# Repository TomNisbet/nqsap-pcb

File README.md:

# NQSAP-PCB

A multi-PCB version of the [NQSAP 8-bit computer](https://tomnisbet.github.io/nqsap/)

Visit the [NQSAP-PCB documentation pages](https://tomnisbet.github.io/nqsap-pcb/) for
detailed design notes and schematics.

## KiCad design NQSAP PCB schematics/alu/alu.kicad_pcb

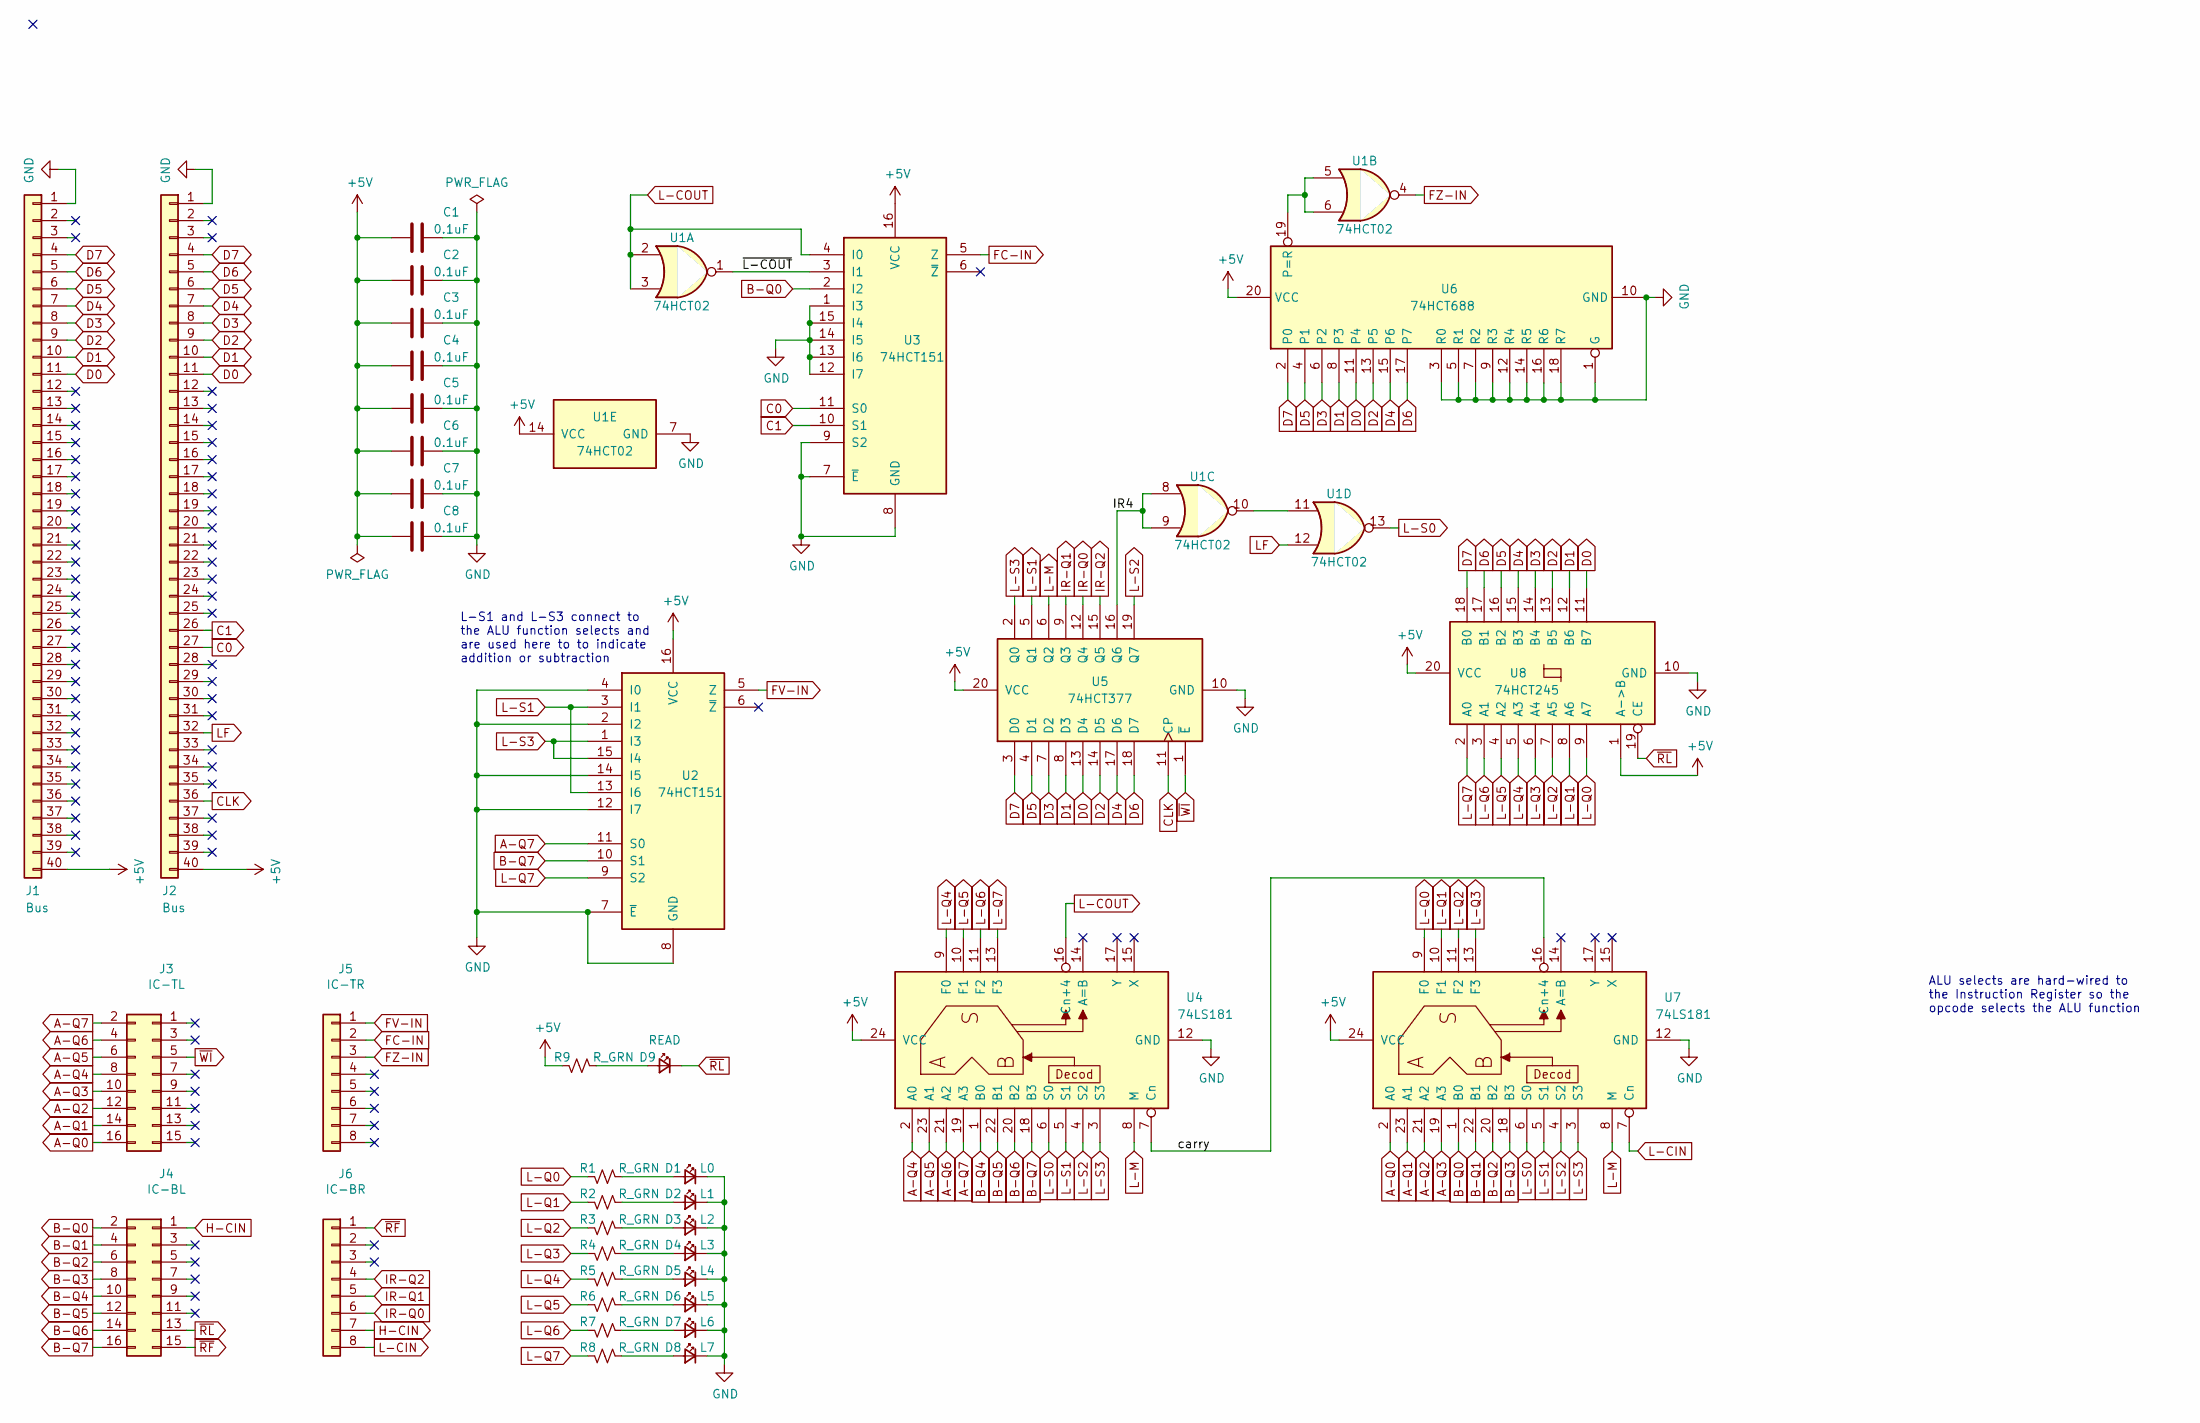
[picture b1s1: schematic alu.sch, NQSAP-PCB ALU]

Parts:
C1, C2, C3, C4, C5, C6, C7, C8: 0.1uF; C_0805_2012Metric_Pad1.18x1.45mm_HandSolder
D1: L0; LED_0805_2012Metric_Pad1.15x1.40mm_HandSolder
D2: L1; LED_0805_2012Metric_Pad1.15x1.40mm_HandSolder
D3: L2; LED_0805_2012Metric_Pad1.15x1.40mm_HandSolder
D4: L3; LED_0805_2012Metric_Pad1.15x1.40mm_HandSolder
D5: L4; LED_0805_2012Metric_Pad1.15x1.40mm_HandSolder
D6: L5; LED_0805_2012Metric_Pad1.15x1.40mm_HandSolder
D7: L6; LED_0805_2012Metric_Pad1.15x1.40mm_HandSolder
D8: L7; LED_0805_2012Metric_Pad1.15x1.40mm_HandSolder
D9: READ; LED_0805_2012Metric_Pad1.15x1.40mm_HandSolder
J1, J2: Bus; PinHeader_1x40_P2.54mm_Vertical
J3: IC-TL; PinHeader_2x08_P2.54mm_Vertical
J4: IC-BL; PinHeader_2x08_P2.54mm_Vertical
J5: IC-TR; PinHeader_1x08_P2.54mm_Vertical
J6: IC-BR; PinHeader_1x08_P2.54mm_Vertical
R1, R2, R3, R4, R5, R6, R7, R8, R9: R_GRN; R_0805_2012Metric_Pad1.20x1.40mm_HandSolder
U1: 74HCT02; DIP-14_W7.62mm
U2, U3: 74HCT151; DIP-16_W7.62mm
U4, U7: 74LS181; DIP-24_W15.24mm_Socket
U5: 74HCT377; DIP-20_W7.62mm
U6: 74HCT688; DIP-20_W7.62mm
U8: 74HCT245; DIP-20_W7.62mm

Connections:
+5V: C1.2, C2.2, C3.2, C4.2, C5.2, C6.2, C7.2, C8.2, J1.40, J2.40, R9.1, U1.14 (VCC), U2.16 (VCC), U3.16 (VCC), U4.24 (VCC), U5.20 (VCC), U6.20 (VCC), U7.24 (VCC), U8.1 (A->B), U8.20 (VCC)
/IR4: U1.8, U1.9, U5.16 (Q6)
/carry: U4.7 (Cn), U7.16 (Cn+4)
/~L-COUT: U1.1, U3.3 (I1)
A-Q0: J3.16, U7.2 (A0)
A-Q1: J3.14, U7.23 (A1)
A-Q2: J3.12, U7.21 (A2)
A-Q3: J3.10, U7.19 (A3)
A-Q4: J3.8, U4.2 (A0)
A-Q5: J3.6, U4.23 (A1)
A-Q6: J3.4, U4.21 (A2)
A-Q7: J3.2, U2.11 (S0), U4.19 (A3)
B-Q0: J4.2, U3.2 (I2), U7.1 (B0)
B-Q1: J4.4, U7.22 (B1)
B-Q2: J4.6, U7.20 (B2)
B-Q3: J4.8, U7.18 (B3)
B-Q4: J4.10, U4.1 (B0)
B-Q5: J4.12, U4.22 (B1)
B-Q6: J4.14, U4.20 (B2)
B-Q7: J4.16, U2.10 (S1), U4.18 (B3)
C0: J2.27, U3.11 (S0)
C1: J2.26, U3.10 (S1)
CLK: J2.36, U5.11 (CP)
D0: J1.11, J2.11, U5.13 (D4), U6.11 (P4), U8.11 (B7)
D1: J1.10, J2.10, U5.8 (D3), U6.8 (P3), U8.12 (B6)
D2: J1.9, J2.9, U5.14 (D5), U6.13 (P5), U8.13 (B5)
D3: J1.8, J2.8, U5.7 (D2), U6.6 (P2), U8.14 (B4)
D4: J1.7, J2.7, U5.17 (D6), U6.15 (P6), U8.15 (B3)
D5: J1.6, J2.6, U5.4 (D1), U6.4 (P1), U8.16 (B2)
D6: J1.5, J2.5, U5.18 (D7), U6.17 (P7), U8.17 (B1)
D7: J1.4, J2.4, U5.3 (D0), U6.2 (P0), U8.18 (B0)
FC-IN: J5.2, U3.5 (Z)
FV-IN: J5.1, U2.5 (Z)
FZ-IN: J5.3, U1.4
GND: C1.1, C2.1, C3.1, C4.1, C5.1, C6.1, C7.1, C8.1, D1.1 (K), D2.1 (K), D3.1 (K), D4.1 (K), D5.1 (K), D6.1 (K), D7.1 (K), D8.1 (K), J1.1, J2.1, U1.7 (GND), U2.2 (I2), U2.4 (I0), U2.7 (~E), U2.8 (GND), U2.12 (I7), U2.14 (I5), U3.1 (I3), U3.7 (~E), U3.8 (GND), U3.9 (S2), U3.12 (I7), U3.13 (I6), U3.14 (I5), U3.15 (I4), U4.12 (GND), U5.10 (GND), U6.1 (G), U6.3 (R0), U6.5 (R1), U6.7 (R2), U6.9 (R3), U6.10 (GND), U6.12 (R4), U6.14 (R5), U6.16 (R6), U6.18 (R7), U7.12 (GND), U8.10 (GND)
H-CIN: J4.1, J6.7
IR-Q0: J6.6, U5.12 (Q4)
IR-Q1: J6.5, U5.9 (Q3)
IR-Q2: J6.4, U5.15 (Q5)
L-CIN: J6.8, U7.7 (Cn)
L-COUT: U1.2, U1.3, U3.4 (I0), U4.16 (Cn+4)
L-M: U4.8 (M), U5.6 (Q2), U7.8 (M)
L-Q0: R1.1, U7.9 (F0), U8.9 (A7)
L-Q1: R2.1, U7.10 (F1), U8.8 (A6)
L-Q2: R3.1, U7.11 (F2), U8.7 (A5)
L-Q3: R4.1, U7.13 (F3), U8.6 (A4)
L-Q4: R5.1, U4.9 (F0), U8.5 (A3)
L-Q5: R6.1, U4.10 (F1), U8.4 (A2)
L-Q6: R7.1, U4.11 (F2), U8.3 (A1)
L-Q7: R8.1, U2.9 (S2), U4.13 (F3), U8.2 (A0)
L-S0: U1.13, U4.6 (S0), U7.6 (S0)
L-S1: U2.3 (I1), U2.13 (I6), U4.5 (S1), U5.5 (Q1), U7.5 (S1)
L-S2: U4.4 (S2), U5.19 (Q7), U7.4 (S2)
L-S3: U2.1 (I3), U2.15 (I4), U4.3 (S3), U5.2 (Q0), U7.3 (S3)
LF: J2.32, U1.12
unnamed: D1.2 (A), R1.2
unnamed: D2.2 (A), R2.2
unnamed: D3.2 (A), R3.2
unnamed: D4.2 (A), R4.2
unnamed: D5.2 (A), R5.2
unnamed: D6.2 (A), R6.2
unnamed: D7.2 (A), R7.2
unnamed: D8.2 (A), R8.2
unnamed: D9.2 (A), R9.2
unnamed: U1.5, U1.6, U6.19 (P=R)
unnamed: U1.10, U1.11
~RF: J4.15, J6.1
~RL: D9.1 (K), J4.13, U8.19 (CE)
~WI: J3.5, U5.1 (~E)

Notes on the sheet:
ALU selects are hard-wired to the Instruction Register so the opcode selects the ALU function
L-S1 and L-S3 connect to the ALU function selects and are used here to to indicate addition or subtraction

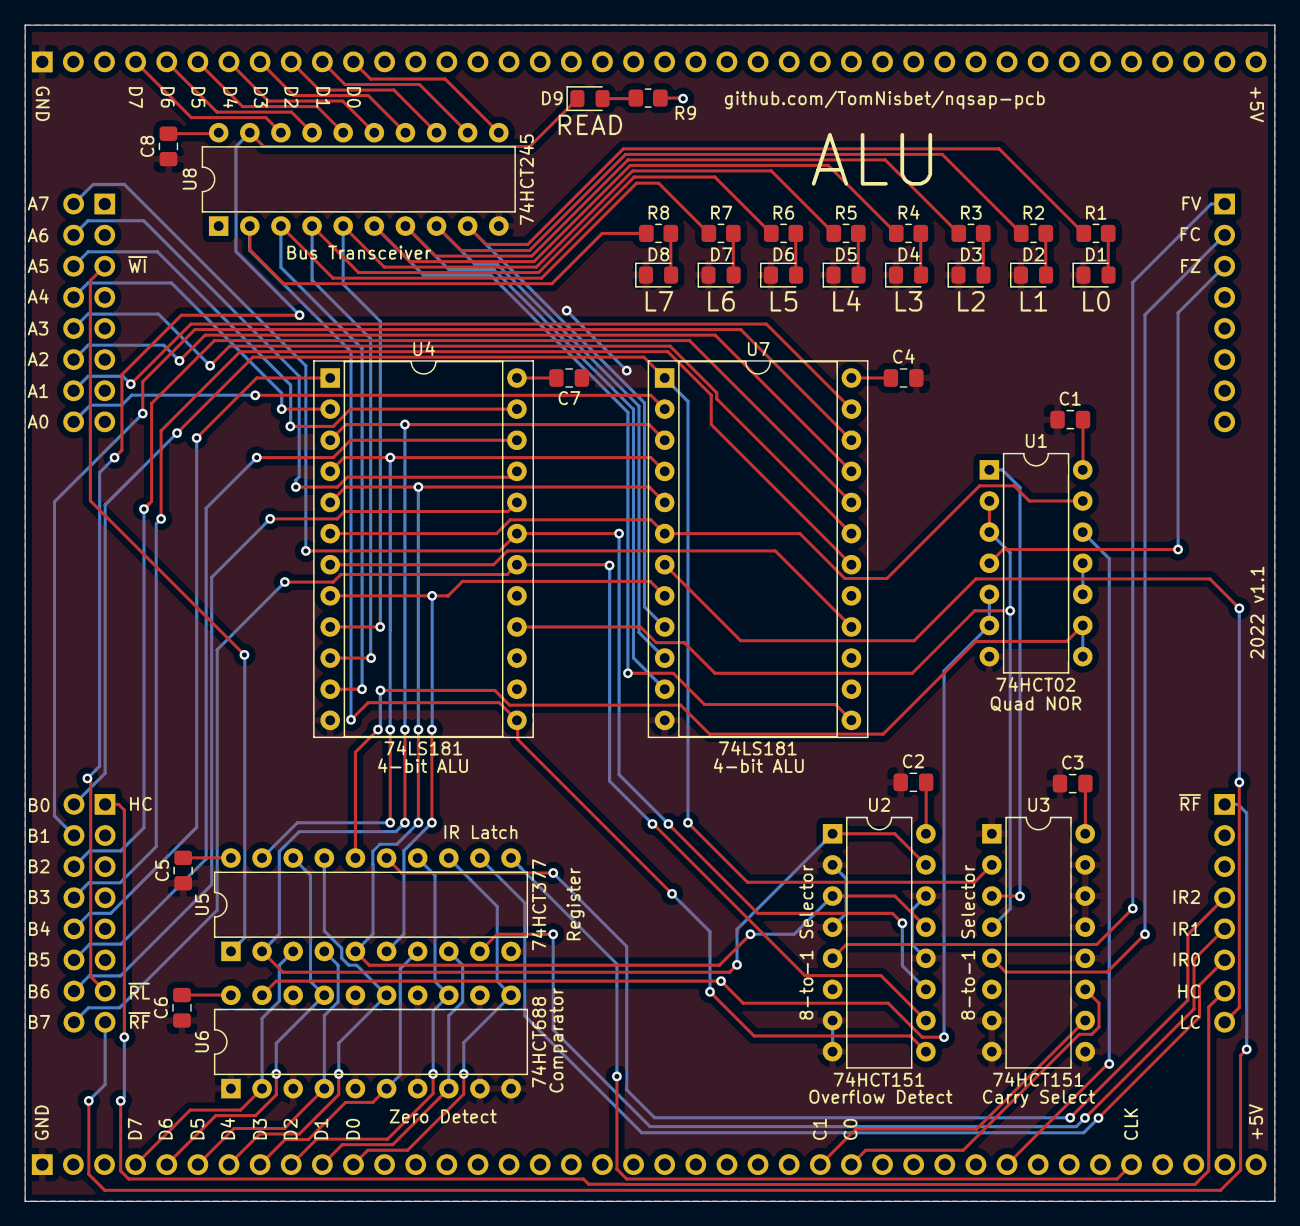
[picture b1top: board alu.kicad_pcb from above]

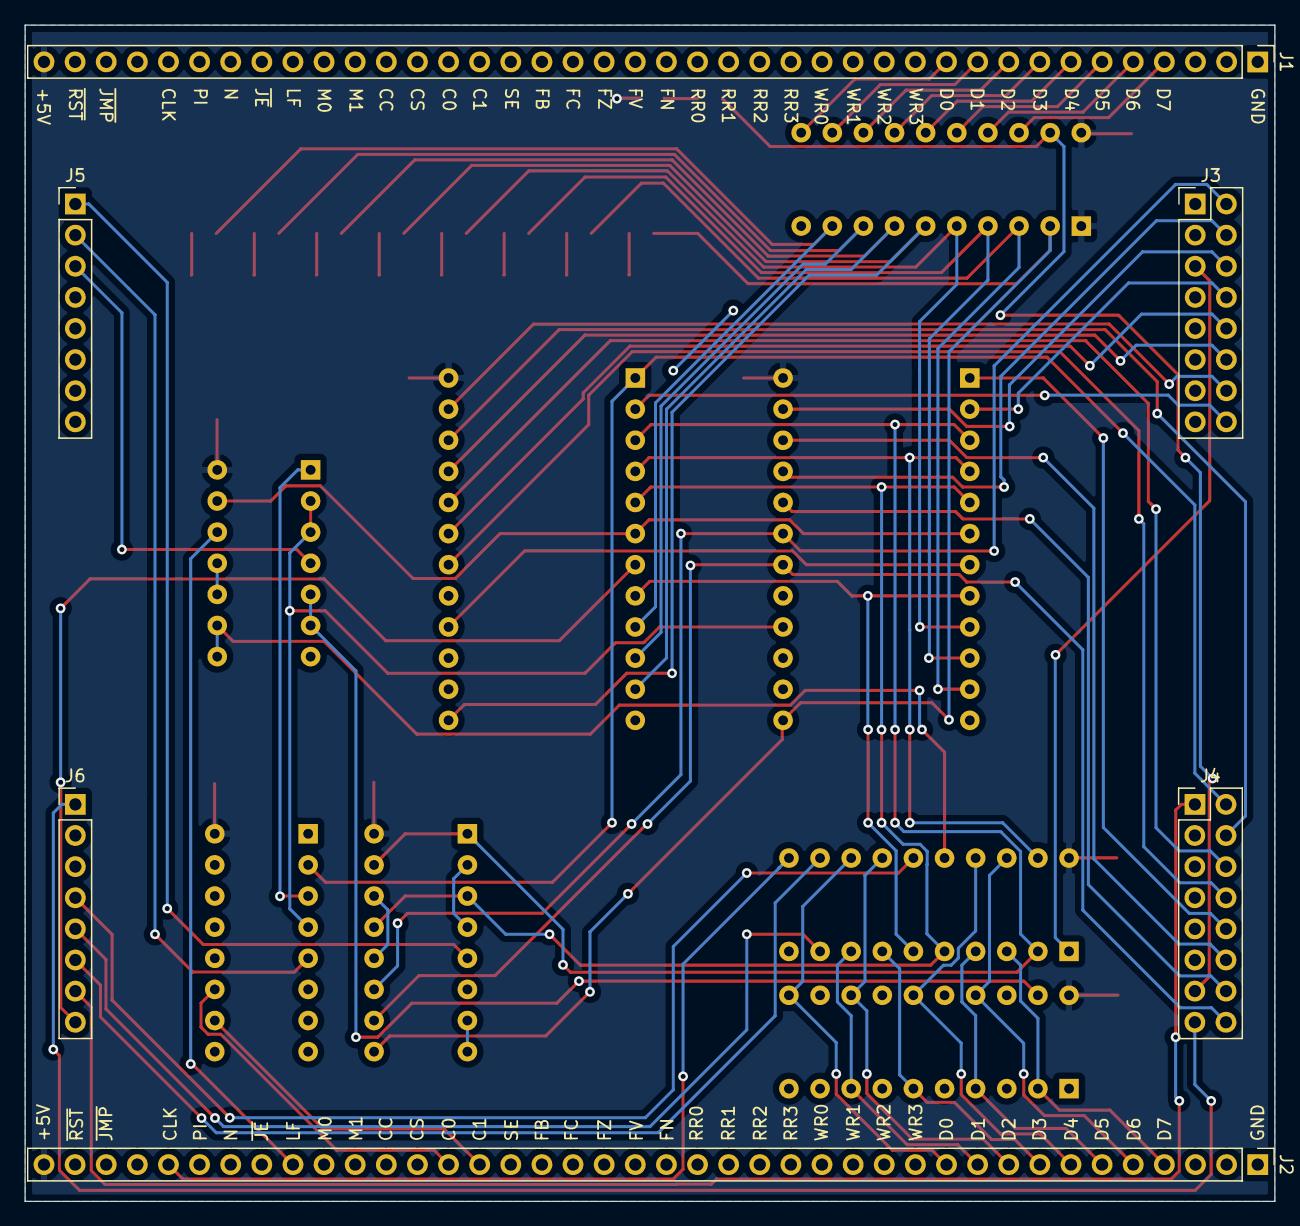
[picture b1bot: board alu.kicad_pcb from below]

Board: 2 copper layers, 102.0 x 96.0 mm, 40 parts (6 on the bottom side), 69 nets.

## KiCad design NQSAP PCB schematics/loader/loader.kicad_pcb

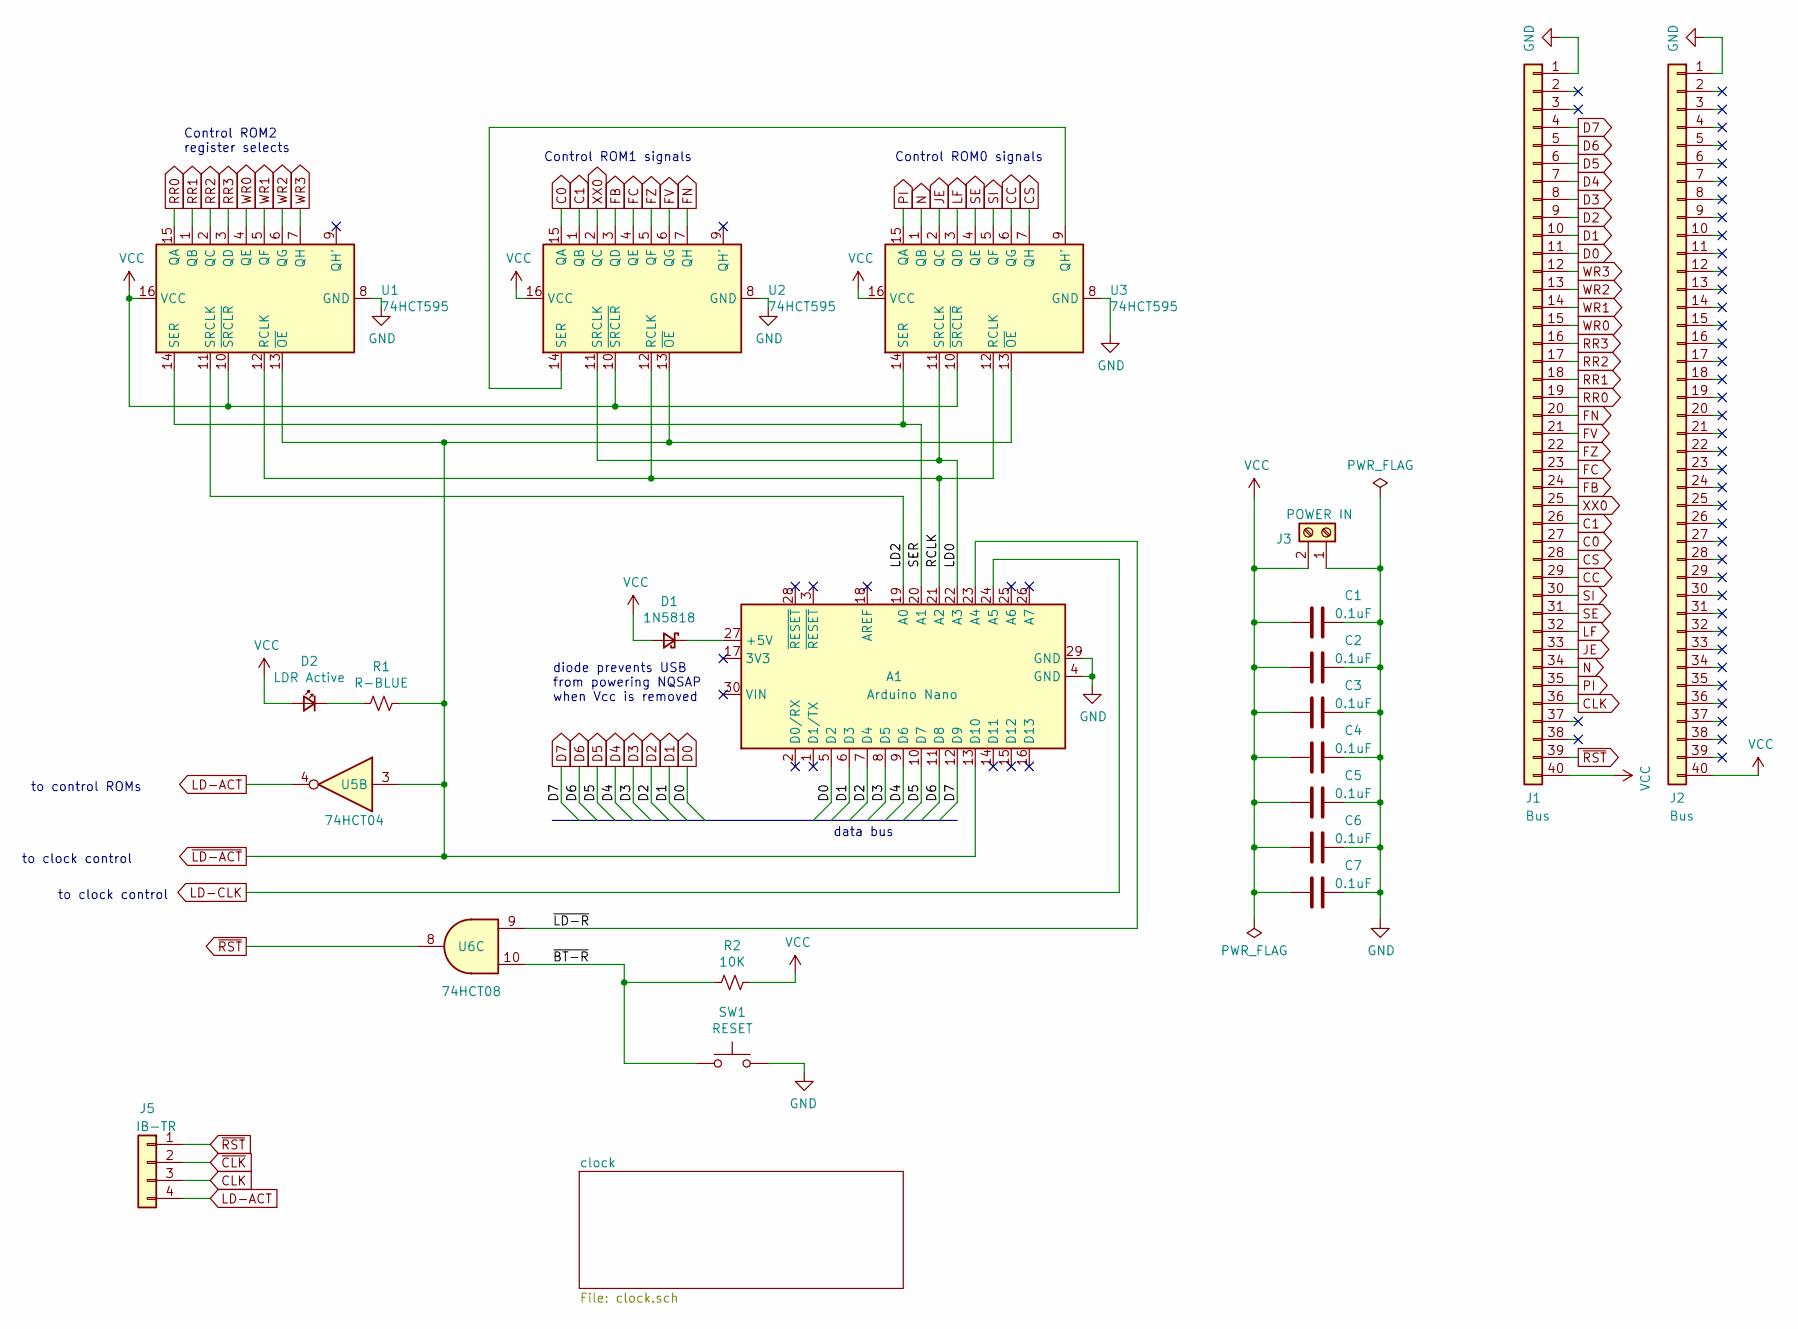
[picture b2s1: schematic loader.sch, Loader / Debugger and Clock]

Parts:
A1: Arduino Nano; Arduino_Nano
C1, C2, C3, C4, C5, C6, C7: 0.1uF; C_0805_2012Metric_Pad1.18x1.45mm_HandSolder
D1: 1N5818; D_DO-41_SOD81_P10.16mm_Horizontal
D2: LDR Active; LED_0805_2012Metric_Pad1.15x1.40mm_HandSolder
J1, J2: Bus; PinHeader_1x40_P2.54mm_Vertical
J3: POWER IN; TerminalBlock_RND_205-00012_1x02_P5.00mm_Horizontal
J5: IB-TR; PinHeader_1x04_P2.54mm_Vertical
R1: R-BLUE; R_0805_2012Metric_Pad1.20x1.40mm_HandSolder
R2: 10K; R_0805_2012Metric_Pad1.20x1.40mm_HandSolder
SW1: RESET; SW_PUSH_6mm
U1, U2, U3: 74HCT595; SOIC-16_3.9x9.9mm_P1.27mm
U5: 74HCT04; DIP-14_W7.62mm
U6: 74HCT08; DIP-14_W7.62mm

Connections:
/LD0: A1.22 (A3), U2.11 (SRCLK), U3.11 (SRCLK)
/LD2: A1.19 (A0), U1.11 (SRCLK)
/RCLK: A1.21 (A2), U1.12 (RCLK), U2.12 (RCLK), U3.12 (RCLK)
/SER: A1.20 (A1), U1.14 (SER), U3.14 (SER)
/~BT-R: R2.2, SW1.2, U6.10
/~LD-R: A1.23 (A4), U6.9
C0: J1.27, U2.15 (QA)
C1: J1.26, U2.1 (QB)
CC: J1.29, U3.6 (QG)
CLK: J1.36, J5.3; also elsewhere on the board
CS: J1.28, U3.7 (QH)
D0: A1.5 (D2), J1.11
D1: A1.6 (D3), J1.10
D2: A1.7 (D4), J1.9
D3: A1.8 (D5), J1.8
D4: A1.9 (D6), J1.7
D5: A1.10 (D7), J1.6
D6: A1.11 (D8), J1.5
D7: A1.12 (D9), J1.4
FB: J1.24, U2.3 (QD)
FC: J1.23, U2.4 (QE)
FN: J1.20, U2.7 (QH)
FV: J1.21, U2.6 (QG)
FZ: J1.22, U2.5 (QF)
GND: A1.4 (GND), A1.29 (GND), C1.1, C2.1, C3.1, C4.1, C5.1, C6.1, C7.1, J1.1, J2.1, J3.1, SW1.1, U1.8 (GND), U2.8 (GND), U3.8 (GND); also elsewhere on the board
JE: J1.33, U3.2 (QC)
LD-ACT: J5.4, U5.4
LD-CLK: A1.24 (A5); also elsewhere on the board
LF: J1.32, U3.3 (QD)
N: J1.34, U3.1 (QB)
unnamed: A1.27 (+5V), D1.1 (K)
unnamed: D2.1 (K), R1.2
unnamed: U2.14 (SER), U3.9 (QH')
PI: J1.35, U3.15 (QA)
RR0: J1.19, U1.15 (QA)
RR1: J1.18, U1.1 (QB)
RR2: J1.17, U1.2 (QC)
RR3: J1.16, U1.3 (QD)
SE: J1.31, U3.4 (QE)
SI: J1.30, U3.5 (QF)
VCC: C1.2, C2.2, C3.2, C4.2, C5.2, C6.2, C7.2, D1.2 (A), D2.2 (A), J1.40, J2.40, J3.2, R2.1, U1.10 (~SRCLR), U1.16 (VCC), U2.10 (~SRCLR), U2.16 (VCC), U3.10 (~SRCLR), U3.16 (VCC); also elsewhere on the board
WR0: J1.15, U1.4 (QE)
WR1: J1.14, U1.5 (QF)
WR2: J1.13, U1.6 (QG)
WR3: J1.12, U1.7 (QH)
XX0: J1.25, U2.2 (QC)
~CLK: J5.2; also elsewhere on the board
~LD-ACT: A1.13 (D10), R1.1, U1.13 (~OE), U2.13 (~OE), U3.13 (~OE), U5.3; also elsewhere on the board
~RST: J1.39, J5.1, U6.8

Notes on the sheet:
data bus
diode prevents USB from powering NQSAP when Vcc is removed
to control ROMs
to clock control
Control ROM2 register selects
Control ROM1 signals
Control ROM0 signals

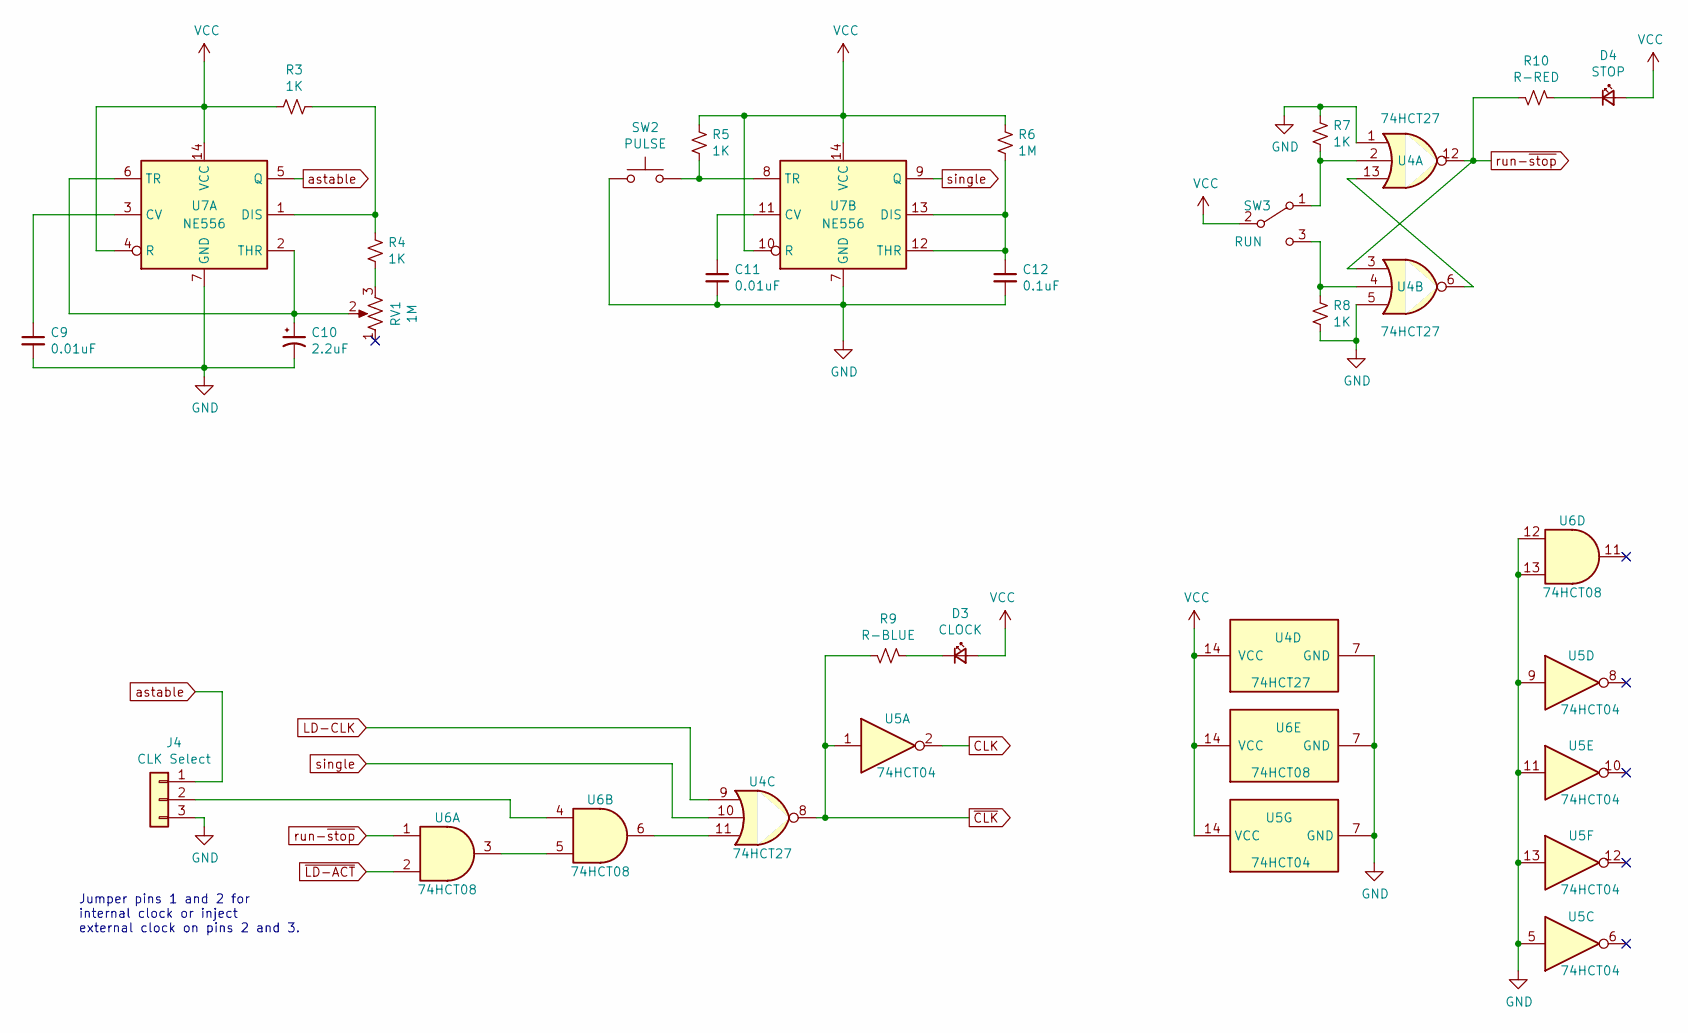
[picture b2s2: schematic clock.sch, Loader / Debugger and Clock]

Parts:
C9, C11: 0.01uF; C_0805_2012Metric_Pad1.18x1.45mm_HandSolder
C10: 2.2uF; C_0805_2012Metric_Pad1.18x1.45mm_HandSolder
C12: 0.1uF; C_0805_2012Metric_Pad1.18x1.45mm_HandSolder
D3: CLOCK; LED_0805_2012Metric_Pad1.15x1.40mm_HandSolder
D4: STOP; LED_0805_2012Metric_Pad1.15x1.40mm_HandSolder
J4: CLK Select; PinHeader_1x03_P2.54mm_Vertical
R3, R4, R5, R7, R8: 1K; R_0805_2012Metric_Pad1.20x1.40mm_HandSolder
R6: 1M; R_0805_2012Metric_Pad1.20x1.40mm_HandSolder
R9: R-BLUE; R_0805_2012Metric_Pad1.20x1.40mm_HandSolder
R10: R-RED; R_0805_2012Metric_Pad1.20x1.40mm_HandSolder
RV1: 1M; Potentiometer_Bourns_3386F_Vertical
SW2: PULSE; SW_PUSH-12mm
SW3: RUN; Switch_Slide_11.6x4mm_EG1218
U4: 74HCT27; DIP-14_W7.62mm
U5: 74HCT04; DIP-14_W7.62mm
U6: 74HCT08; DIP-14_W7.62mm
U7: NE556; DIP-14_W7.62mm

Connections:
CLK: U5.2; also elsewhere on the board
GND: C9.2, C10.2, C11.2, C12.2, J4.3, R7.1, R8.2, SW2.1, U4.1, U4.5, U4.7 (GND), U5.5, U5.7 (GND), U5.9, U5.11, U5.13, U6.7 (GND), U6.12, U6.13, U7.7 (GND); also elsewhere on the board
LD-CLK: U4.9; also elsewhere on the board
unnamed: C9.1, U7.3 (CV)
unnamed: C10.1, RV1.2, U7.2 (THR), U7.6 (TR)
unnamed: C11.1, U7.11 (CV)
unnamed: C12.1, R6.2, U7.12 (THR), U7.13 (DIS)
unnamed: D3.1 (K), R9.2
unnamed: D4.1 (K), R10.2
unnamed: J4.2, U6.4
unnamed: R3.1, R4.2, U7.1 (DIS)
unnamed: R4.1, RV1.3
unnamed: R5.2, SW2.2, U7.8 (TR)
unnamed: R7.2, SW3.1 (A), U4.2
unnamed: R8.1, SW3.3 (C), U4.4
unnamed: U4.11, U6.6
unnamed: U4.6, U4.13
unnamed: U6.3, U6.5
VCC: D3.2 (A), D4.2 (A), R3.2, R5.1, R6.1, SW3.2 (B), U4.14 (VCC), U5.14 (VCC), U6.14 (VCC), U7.4 (R), U7.10 (R), U7.14 (VCC); also elsewhere on the board
astable: J4.1, U7.5 (Q)
run-~stop: R10.1, U4.3, U4.12, U6.1
single: U4.10, U7.9 (Q)
~CLK: R9.1, U4.8, U5.1; also elsewhere on the board
~LD-ACT: U6.2; also elsewhere on the board

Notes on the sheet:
Jumper pins 1 and 2 for internal clock or inject external clock on pins 2 and 3.

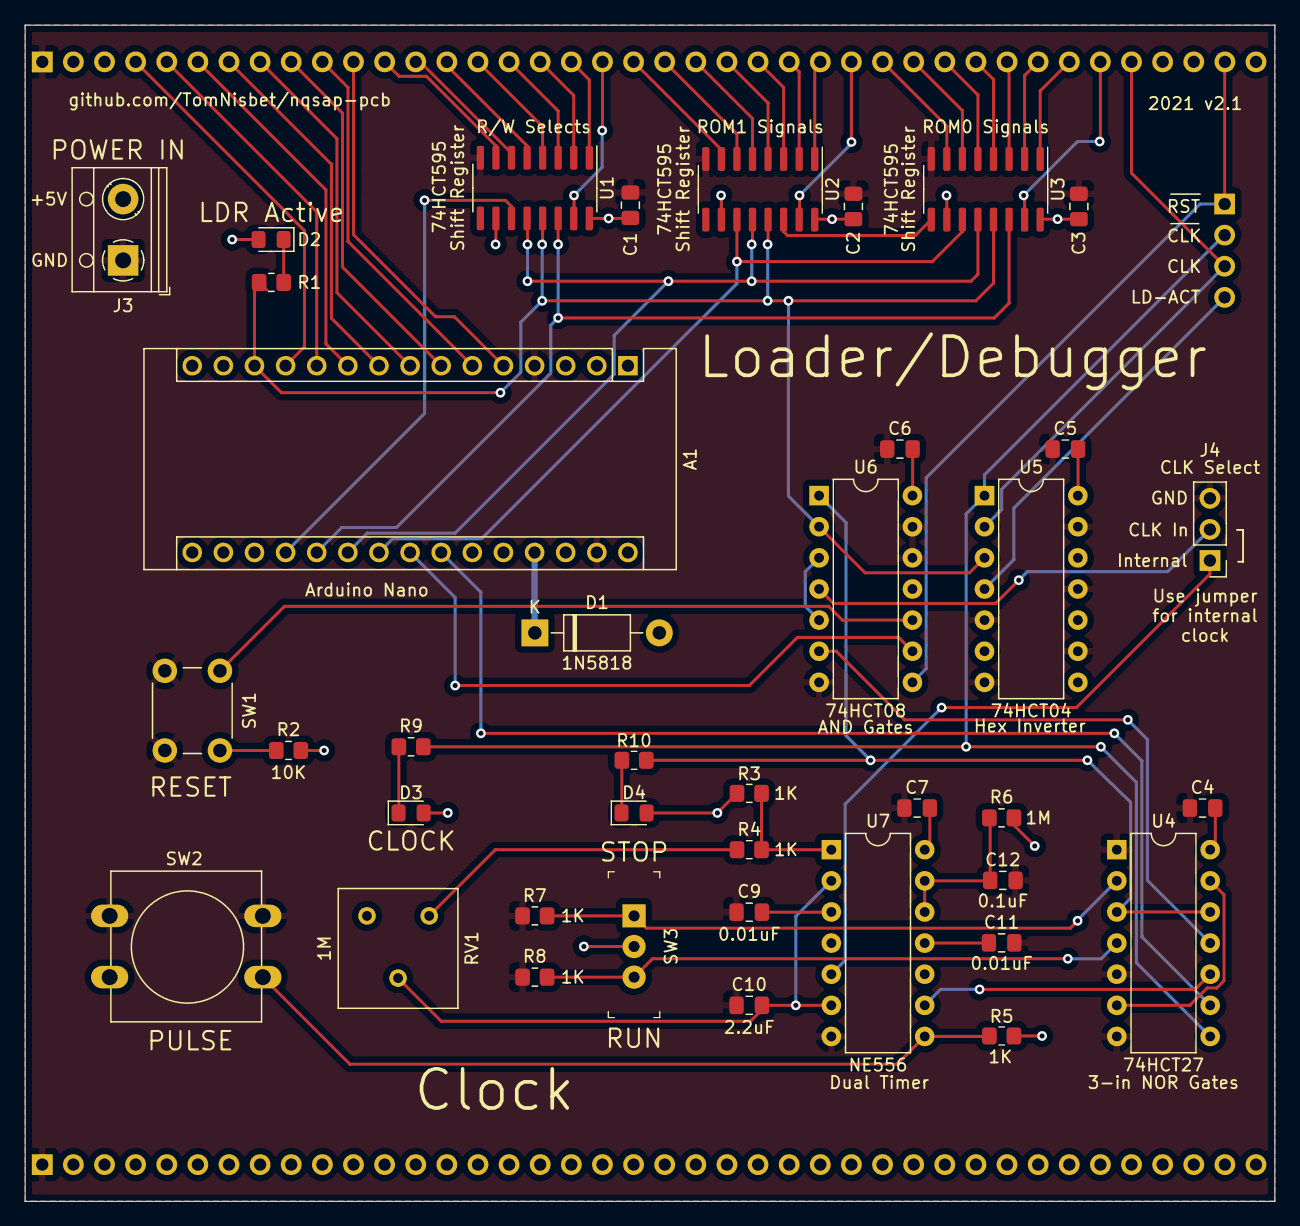
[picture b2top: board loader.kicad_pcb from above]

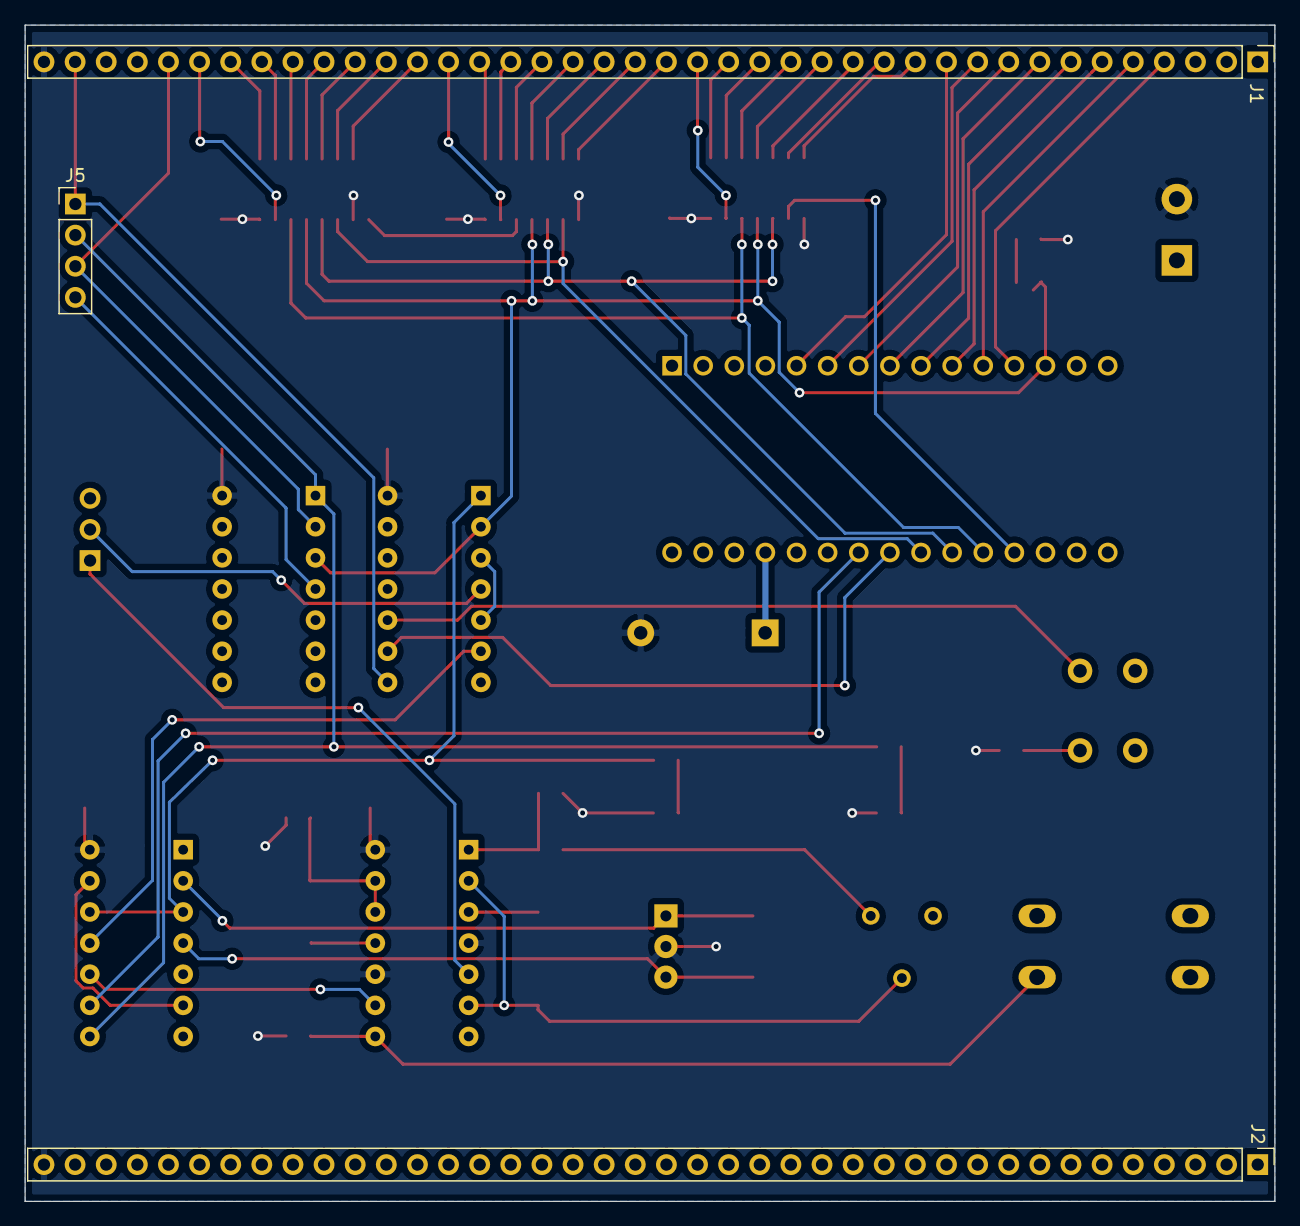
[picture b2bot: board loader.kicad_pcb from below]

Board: 2 copper layers, 102.0 x 96.0 mm, 42 parts (3 on the bottom side), 67 nets.
